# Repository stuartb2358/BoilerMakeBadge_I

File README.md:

BoilerMakeBadge_I
=================

A repository for the electronic badge to be distributed at the BoilerMake Hackathon in 2014

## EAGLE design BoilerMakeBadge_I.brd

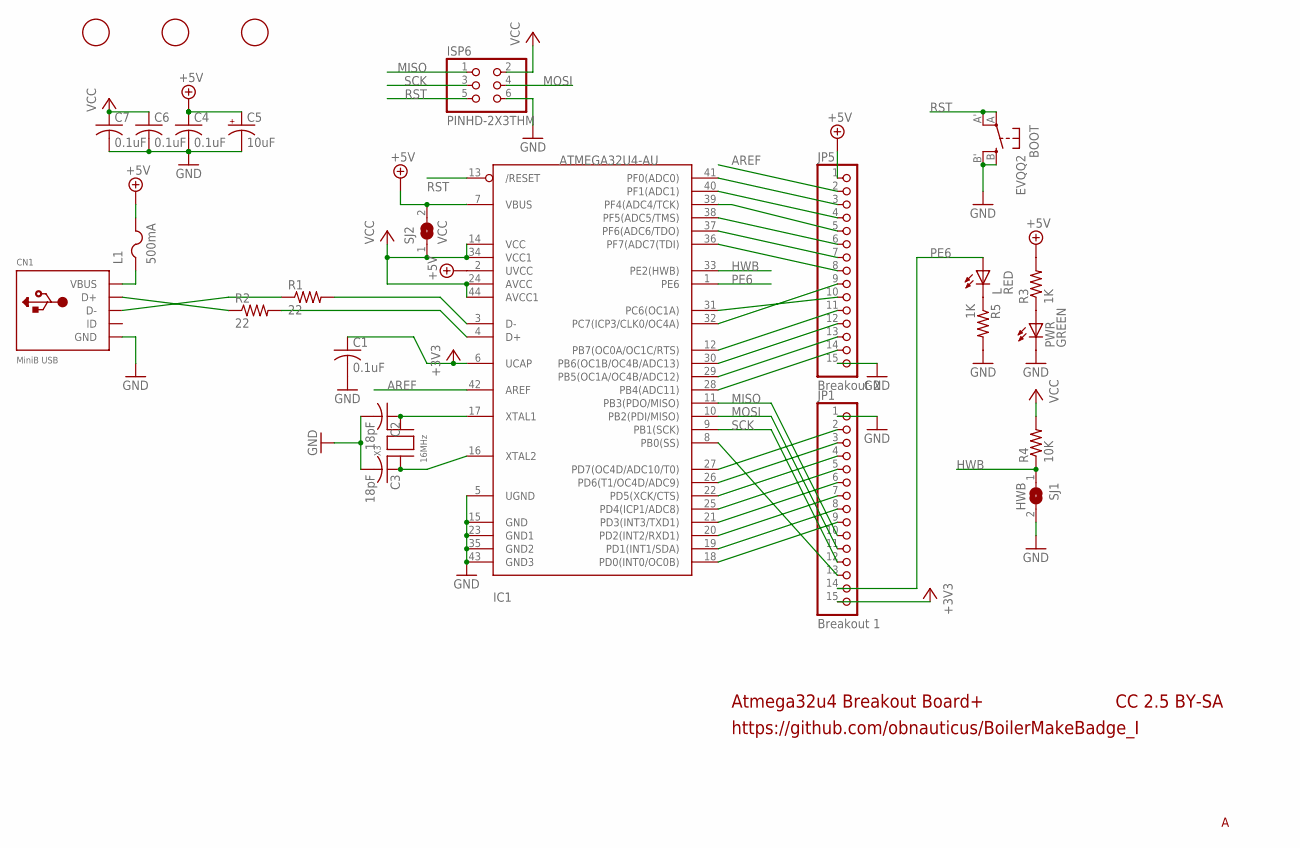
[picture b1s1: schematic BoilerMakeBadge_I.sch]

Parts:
BOOT: EVQQ2; EVQ-Q2
C1, C4, C6, C7: 0.1uF; C0805K
C2, C3: 18pF; C0805K
C5: 10uF; A/3216-18R
CN1: MiniB USB; USB-MINIB
IC1: ATMEGA32U4-AU; TQFP44
ISP6: PINHD-2X3THM; ISP6
JP1: Breakout 1; 1X15-CB
JP5: Breakout 2; 1X15-CB
L: RED; CHIPLED_0805
L1: 500mA; R1206
PWR: GREEN; CHIPLED_0805
R1, R2: 22; R0805
R3, R5: 1K; R0805
R4: 10K; R0805
SJ1: HWB; SJ
SJ2: VCC; SJ
U$1, U$2, U$6: FIDUCIAL; FIDUCIAL_1MM
X3: 16MHz; NX5032

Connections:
+3V3: C1.1, IC1.6 (UCAP), JP1.15
+5V: C4.1, C5.+, IC1.2 (UVCC), IC1.7 (VBUS), JP5.1, L1.2, R3.2, SJ2.2
AREF: IC1.42 (AREF), JP5.2
GND: BOOT.B (S), BOOT.B' (S1), C1.2, C2.2, C3.2, C4.2, C5.-, C6.2, C7.2, CN1.GND, IC1.5 (UGND), IC1.15 (GND), IC1.23 (GND1), IC1.35 (GND2), IC1.43 (GND3), ISP6.6, JP1.1, JP5.15, PWR.C, R5.2, SJ1.2
HWB: IC1.33 (PE2(HWB)), R4.1, SJ1.1
MISO: IC1.11 (PB3(PDO/MISO)), ISP6.1, JP1.10
MOSI: IC1.10 (PB2(PDI/MISO)), ISP6.4, JP1.11
unnamed: PWR.A, R3.1
unnamed: CN1.D+, R2.1
unnamed: IC1.3 (D-), R1.2
unnamed: IC1.4 (D+), R2.2
unnamed: CN1.D-, R1.1
unnamed: C2.1, IC1.17 (XTAL1), X3.P$2
unnamed: C3.1, IC1.16 (XTAL2), X3.P$1
unnamed: L.C, R5.1
PB0: IC1.8 (PB0(SS)), JP1.13
PB4: IC1.28 (PB4(ADC11)), JP5.14
PB5: IC1.29 (PB5(OC1A/OC4B/ADC12)), JP5.13
PB6: IC1.30 (PB6(OC1B/OC4B/ADC13)), JP5.12
PB7: IC1.12 (PB7(OC0A/OC1C/RTS)), JP5.11
PC6: IC1.31 (PC6(OC1A)), JP5.10
PC7: IC1.32 (PC7(ICP3/CLK0/OC4A)), JP5.9
PD0: IC1.18 (PD0(INT0/OC0B)), JP1.9
PD1: IC1.19 (PD1(INT1/SDA)), JP1.8
PD2: IC1.20 (PD2(INT2/RXD1)), JP1.7
PD3: IC1.21 (PD3(INT3/TXD1)), JP1.6
PD4: IC1.25 (PD4(ICP1/ADC8)), JP1.5
PD5: IC1.22 (PD5(XCK/CTS)), JP1.4
PD6: IC1.26 (PD6(T1/OC4D/ADC9)), JP1.3
PD7: IC1.27 (PD7(OC4D/ADC10/T0)), JP1.2
PE6: IC1.1 (PE6), JP1.14, L.A
PF0: IC1.41 (PF0(ADC0)), JP5.3
PF1: IC1.40 (PF1(ADC1)), JP5.4
PF4: IC1.39 (PF4(ADC4/TCK)), JP5.5
PF5: IC1.38 (PF5(ADC5/TMS)), JP5.6
PF6: IC1.37 (PF6(ADC6/TDO)), JP5.7
PF7: IC1.36 (PF7(ADC7(TDI)), JP5.8
RST: BOOT.A, BOOT.A' (P1), IC1.13 (/RESET), ISP6.5
SCK: IC1.9 (PB1(SCK)), ISP6.3, JP1.12
VBUS: CN1.VBUS, L1.1
VCC: C6.1, C7.1, IC1.14 (VCC), IC1.24 (AVCC), IC1.34 (VCC1), IC1.44 (AVCC1), ISP6.2, R4.2, SJ2.1

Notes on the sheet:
Atmega32u4 Breakout Board+
https://github.com/obnauticus/BoilerMakeBadge_I
CC 2.5 BY-SA

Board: 2 copper layers, 27 parts (0 on the bottom side), 41 nets, no tracks yet.

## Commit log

2014-09-07 adding preliminary bill of materials
2014-09-08 adding skeleton schematic
2014-09-08 removing shitty skeleton project
2014-09-09 Added Altium PCB schematic, PCB parts library, & updated BOM.
2014-09-10 added dual package FET to replace diode and single FET to reduce part count.
2014-09-11 toplel
2014-09-11 adding nRF24L01+ Library
2014-09-11 adding nRF24L01+ Librariy copied from other user
2014-09-12 Schematic for Rev A Done!
2014-09-12 adding PCB Doc with octagin (ew)
2014-09-12 fixed capacitors
2014-09-13 commiting new XTAL pads
2014-09-13 modifying octagon layout
2014-09-13 RF partially routed
2014-09-13 replacing zener regulator with 7803
2014-09-14 adding updated BOM
2014-09-14 Added second PCB design.
2014-09-14 Routed micro pin headers.
2014-09-14 adding RF section, pours still manditory
2014-09-14 Fixed labels on RF cluster.
2014-09-15 Routed LEDs.
2014-09-15 Finished major routing.
2014-09-15 Created negative overlay.
2014-09-15 overlay sort-of finished
2014-09-15 finished overlay, added F Antenna component
2014-09-15 Routed RF subsystem.
2014-09-15 Created ground pour dxf.
2014-09-15 Fixed ground pour dcf.
2014-09-16 planes fixed
2014-09-16 Added pours for VCC.
2014-09-16 adding 3V3 groundpour, weird supervisor badge completed
2014-09-16 adding square-ish layout variant with BM logo
2014-09-16 prototype bom finished for sierra circuits
2014-09-16 Routed squareish badge design.
2014-09-16 squarish design finished, with fid markers, pours, etc
2014-09-16 adding annotations to BOM
2014-09-16 adding CAM output
2014-09-18 Generated gerbers.
2014-09-19 Fixed ground pour short.
2014-09-22 Fixed BOM.
2014-09-24 Updated gerbers/PnP files.
2014-10-01 added badge bulk program
2014-10-06 adding errata
